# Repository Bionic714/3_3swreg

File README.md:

3_3swreg
========

3.3v switching reg.  

IC
-----
http://www.mouser.com/ProductDetail/Skyworks-Solutions-Inc/AAT1110IJS-33-T1/?qs=sGAEpiMZZMsujgvXkMPlDY3niuAtBycJ  

Inductor
-----
http://www.mouser.com/ProductDetail/Bourns/SRN5020-4R7M/?qs=sGAEpiMZZMsg%252by3WlYCkUw2KTUPRwVFvTnvIgWPwTAI%3d  

Mouser cart
-----
http://www.mouser.com/ProjectManager/ProjectDetail.aspx?AccessID=9bcecfff61

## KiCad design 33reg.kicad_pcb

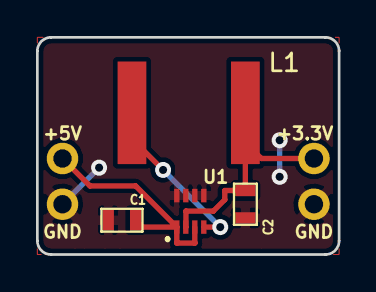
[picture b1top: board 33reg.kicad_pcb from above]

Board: 2 copper layers, 16.8 x 12.1 mm, 8 parts (0 on the bottom side), 4 nets.

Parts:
+3.3V, +5V: TST; TEST_0.100
C1, C2: C; SM0603
GND: TST; TEST_0.100
GND#2: TST; TEST_0.100
L1: INDUCTOR; inductor_SRN5020
U1: AAT1110IJS-3.3-T1; SC70JW-8

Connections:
+3.3v: +3.3V.1, C2.2, L1.1, U1.2
+5v: +5V.1, C1.1, U1.1, U1.3
GND: C1.2, C2.1, GND.1, GND#2.1, U1.5, U1.6, U1.7, U1.8
unnamed: L1.2, U1.4

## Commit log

2013-10-14 kicadlib
2013-10-14 proj & sch
2013-10-14 add reg ic + circuit
2013-10-14 annotate and netlist
2013-10-14 start pcb
2013-10-14 pcb done, add gerbers+drill
2013-10-14 add pics
2013-10-14 add osh park upload archive
2013-11-07 - add values for caps
2013-11-07 - add sample 4 switch buck-boost circuit
2013-11-07 - add input cap to 4 switcher
